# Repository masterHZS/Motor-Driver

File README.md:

# 电机驱动项目 — 总索引

**HC32F005 单板三相无刷电机驱动**

当前主线：

```text
上位机 HostSoftware
  -> USB-TTL / DAPLink 虚拟串口
  -> F005_Slave（Modbus-RTU 从站，地址 1）
  -> 20 kHz PWM 三相功率级
  -> 2216-730KV 三相无刷电机
```

工作方法见 `工作流程.txt`。每个顶层目录均有本地 `00_索引.md`。

> 🤖 **AI / 自动化代理首次进入请先读 `00_AI/START_HERE.md`**（入口与硬禁令）；
> 机器可读清单在 `00_AI/manifest.json`，根目录 `AGENTS.md` 是自动加载的入口钩子。

---

## 1. 顶层顺序与标签

| 顺序 | 目录 | 标签 | 内容 |
|---:|---|---|---|
| 00 | `00_AI/` | AI 入口、现状快照 | ★ **AI 首读**：入口说明、项目地图、当前状态、权威文件速查、构建命令、踩坑与硬约束 |
| 01 | `01_PCB/` | 主设计、已冻结、审核 | V3.1 原理图、网表、BOM、生成器、审核报告 |
| 02 | `02_固件/` | 主固件、通信、台架 | F005 从机、F072 桥/旧控制器参考 |
| 03 | `03_上位机/` | 主软件、Modbus 主站 | Qt 6 + QML 源码与 Release |
| 04 | `04_工作区/` | 调试、波形、审核、工具 | 波形、日志、Gerber 审核、ISP 工具 |
| 05 | `05_采购清单/` | 采购、执行记录 | 采购申请单 |
| 06 | `06_参考资料/` | 唯一资料库 | 芯片知识库、开源参考、EasyEDA、历史会话 |
| 99 | `99_归档/` | 历史、待评估删除 | 旧固件和旧版图备份 |

标签含义：

- `[主]`：当前维护和交付入口。
- `[冻结]`：已作为当前硬件依据，不随意修改。
- `[参考]`：用于查阅或对照，不进入主构建。
- `[调试]`：实测数据和过程记录。
- `[历史]`：只作追溯，可能清理。
- `[可重建]`：构建产物、缓存或派生产物。

---

## 2. 推荐查看顺序

0. `00_AI/START_HERE.md` → `00_AI/02_当前状态.md`（AI 与首次接触者入口）
1. `01_PCB/00_索引.md`
2. `01_PCB/说明.md`
3. `01_PCB/Motor-project/V3.1_升级说明.md`
4. `01_PCB/Motor-project/V3.0_设计规格与计算书.md`
5. `01_PCB/Motor-project/motor-driver-V3.1.*`
6. `01_PCB/Motor-analysis/HC32F005_引脚分配.md`
7. `02_固件/00_索引.md`
8. `02_固件/F005_COMMS.md`
9. `02_固件/F072_MotorCtrl/README.md`
10. `03_上位机/00_索引.md` 与 `03_上位机/HostSoftware/README.md`
11. `04_工作区/00_索引.md`
12. `06_参考资料/00_索引.md`

> ⚠️ **路径提示**：旧文档里写的 `01_PCB/01_工程/` = 现在的 **`01_PCB/Motor-project/`**，
> `01_PCB/03_审核/` = 现在的 **`01_PCB/Motor-analysis/`**（2026-10 改名，历史记录未逐一改写）。

---

## 3. 当前主链路

### 硬件

- 当前版本：**V3.1**（原理图冻结、PCB 已打样；板上 F005 已拆除，改外接 F072 直驱）
- 母线：12.0–16.8 V，4S（有效窗口 13.5–16.8 V）
- 主控：HC32F005C6PA（板上位号 U5，**当前空位**）
- 栅驱动：FD6288T
- 当前控制器：外接 **HC32F072JATA** → `TP12`–`TP17`（见 `02_固件/F072_MotorCtrl/`）

### F005 从机

- 默认构建：`02_固件/F005_Slave/build_comms.ps1`
- 默认输出：`02_固件/F005_Slave/build_comms/comms.hex`
- 通信：UART0，`9600-8N1`，Modbus-RTU 地址 1
- 控制：`0x0002` 油门 0～100
- 实际占空比：默认限幅到 25%
- 开环电换相范围：默认 10～120 Hz
- 非零油门隐式启动，零油门停止
- 烧录恢复：`flash_under_reset.ps1`

### 上位机

- 源码：`03_上位机/HostSoftware/`
- 发布版：`03_上位机/release/HostSoftware/`
- 功能码：`0x03` 读寄存器、`0x06` 写单寄存器
- 状态轮询：`0x0000～0x0009`

---

## 4. 目录维护规则

1. 顶层目录保持两位数字前缀，按开发顺序排列。
2. 每个顶层目录使用 `00_索引.md` 说明标签、内容、顺序和清理规则。
3. 源码工程不按外观随意改名；优先通过索引分类，防止硬编码路径失效。
4. 数据手册和芯片结论只写入 `06_参考资料/芯片知识库/`。
5. 第三方完整工程只写入 `06_参考资料/开源参考工程/`。
6. 构建产物、`__pycache__`、`.pyc`、临时日志可重建或可删除。
7. 历史版本进入 `99_归档/`，不要与当前版本混放。
8. 同内容文件不再保存多份实体副本。
9. `00_AI/` 是 AI 入口与现状快照，只写「指针 + 状态」，不复制权威数据；状态变化后同步更新。

---

## 5. 2026-09-30 整理结果

- F005 主目录收敛为：`build_comms + cmsis + core + ldscripts + port + third_party + user`。
- 删除另一套精简 DDL，只保留官方完整 DDL。
- 删除历史 `build_*`、探针源码、旧 release、便携 Python、测试临时文件。
- 删除根 `$null`、`02_固件/%SystemDrive%`、旧锁文件和可重建缓存。
- `asac-esc` 从固件主目录移到 `06_参考资料/开源参考工程/`。
- 重复 HC32F005 手册合并到 `06_参考资料/芯片知识库/_datasheet/`。
- 所有顶层目录增加 `00_索引.md`，统一标签和推荐查看顺序。

---

## 6. 当前状态

| 项目 | 状态 |
|---|---|
| PCB V3.1 | 已冻结并打样，实板调试中（详见 `01_PCB/说明.md`） |
| 板上 F005 | **已拆除**（UART 固件释放 P27 后 SWD 无法恢复，板上无 nRESET 可用） |
| 当前主链路 | HostSoftware → DAPLink 串口 → **外接 F072_MotorCtrl (`-Direct`)** → V3.1 功率级 |
| F005 直连 Modbus 从站 | 已实现并成功构建（005 拆板前验证通过，保留参考） |
| 上位机油门写 `0x0002` | 已接通 F072 直接油门控制 |
| 电机带载验证 | 尚未完成，必须限流并从低油门开始 |
| 开环版带电机 | ⛔ **已明令禁止**（2026-10-08 剧烈震动事故），必须用 BEMF 闭环 |
| BEMF 闭环 | `F072_MotorCtrl -BEMF`，ADC 通道映射已验证，待整机联调 |

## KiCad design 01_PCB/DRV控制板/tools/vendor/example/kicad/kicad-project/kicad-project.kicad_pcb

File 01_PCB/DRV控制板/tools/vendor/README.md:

中文 | [English](README.en.md)

# kicad-to-easyeda-eprj3

将 KiCAD 工程文件转换为嘉立创EDA（EasyEDA Pro）的 eprj3 工程格式，并将 KiCad 库转换为嘉立创EDA库文件 `.elibz2`。Convert KiCAD project files to the eprj3 project format of EasyEDA Pro, and KiCad libraries to the EasyEDA Pro library format `.elibz2`.

## 功能

- **工程转换**：批量遍历目录下所有 `.kicad_sch` / `.kicad_pcb`，生成完整的 eprj3 文件夹工程（`<name>.eprj3` 索引 + `sch/` + `pcb/`）
- **库转换**：把一个目录下的全部 KiCad 库（`*.kicad_sym` 符号库 + `*.pretty/*.kicad_mod` 封装库）打包成一个嘉立创EDA专业版库文件 `.elibz2`

## 环境要求

- Node.js ≥ 18，无任何 npm 依赖。

## 用法

### 1) KiCad 工程 → eprj3 工程（批量）

```bash
node scripts/convert-kicad.js convert <KiCad工程目录> <输出目录> [--project-name <名称>]
```

案例 — 转换本仓库自带的示例工程：

```bash
node scripts/convert-kicad.js convert example/kicad/kicad-project ./eprj3 --project-name kicad-project
```

输出：

```text
Created eprj3 project at D:/…/eprj3
  sch: kicad-project.kicad_sch -> D:/…/eprj3/sch/Schematic1/P1.esch2
  pcb: kicad-project.kicad_pcb -> D:/…/eprj3/pcb/PCB1.epcb2
```

生成的工程可直接用嘉立创EDA专业版打开：`<输出目录>/kicad-project.eprj3`，内含 `sch/`（原理图）与 `pcb/`（PCB）。

- 两个目录按位置传入：第 1 个是 KiCad 工程目录，第 2 个是 eprj3 输出目录
- 工程目录下每个 `*.kicad_sch` 生成一张原理图（`Schematic1`、`Schematic2` …），每个 `*.kicad_pcb` 生成一块板（`PCB1`、`PCB2` …）

### 2) KiCad 库目录 → 嘉立创EDA库包 .elibz2

```bash
node scripts/convert-kicad-lib.js convert <KiCad库目录> <输出.elibz2> [--name <库名>]
```

案例 — 把符号库与封装库放进同一个目录后整体打包（目录扫描不递归，`.kicad_sym` 与 `.pretty/` 需是直接子项）：

```text
mylibs/
├── Device.kicad_sym
├── LED.kicad_sym
├── Resistor_SMD.pretty/
│   ├── R_0805_2012Metric.kicad_mod
│   └── …
└── LED_SMD.pretty/
    └── …
```

```bash
node scripts/convert-kicad-lib.js convert mylibs ./DeviceLED.elibz2 --name DeviceLED
```

输出：

```text
  sym lib: Device.kicad_sym (533 symbols)
  sym lib: LED.kicad_sym (63 symbols)
  footprint lib: LED_SMD.pretty (100 footprints)
  footprint lib: Resistor_SMD.pretty (67 footprints)
Wrote DeviceLED.elibz2: 596 symbols, 167 footprints (636245 bytes)
```

生成的 `DeviceLED.elibz2` 可通过嘉立创EDA专业版的库导入功能安装到本地库中。

- 扫描目录下所有 `*.kicad_sym`（符号库）与 `*.pretty/`（封装库，读取其中 `*.kicad_mod`），全部合并写入**一个** `.elibz2`
- `--name` 可选：覆盖包名（默认取输出文件名去掉 `.elibz2` 后缀）
- `.elibz2` 是 zip 压缩包，内含：
  - `device2.json` — 器件/符号/封装索引（uuid → 元数据）；符号 `docType:2`、封装 `docType:4`，每个符号自动生成一个器件条目
  - `<库名>.elibu` — 记录流（与 `.esch2`/`.epcb2` 同格式），每个符号/封装写成两段：`DOCHEAD+META` 与 `DOCHEAD+记录`
- 符号 `Footprint` 属性（如 `Resistor_SMD:R_0805`）与转换出的封装名匹配时，器件的 `Footprint` 属性自动关联到对应封装 uuid
- 电源符号（`symbol_type "power"`）的 META `docType` 写为 18；封装文档包含 19 层表 + `ACTIVE_LAYER` + 完整 `CANVAS`，且不带 `PART` 记录
- 示例：`example/easyeda/easyeda-pro-libs.elibz2` 为嘉立创EDA专业版导出的参考库包

## 转换覆盖范围（best-effort）

输出严格对齐 [easyeda-pro-format-skill](https://github.com/easyeda/easyeda-pro-format-skill) 的官方格式文档（types / 字段定义 / JSON Schemas），并以真实导出数据校准 schema 与实际导出不一致之处；可另参考 [官方 eprj3 格式示例工程](https://github.com/easyeda/easyeda-pro-eprj3-format)：

| KiCad | eprj3 |
| --- | --- |
| `lib_symbols`（原理图内嵌符号库） | `.esch2` 内嵌 `SYMBOL` 文档段（`PART`/图形/引脚）+ `DEVICE` 文档段 |
| `symbol` 实例（含 `property`、`mirror`） | `COMPONENT`（`partId` 指向内嵌 `PART`，`DeviceName` 指向 `DEVICE`，镜像/旋转已换算）+ `Designator`/`Value` `ATTR` |
| `wire` | `WIRE` + 多条共享 `lineGroup` 的 `LINE` |
| `bus` / `bus_entry` | `BUS` + `LINE` / `BUSENTRY` |
| `junction` | 填充 `CIRCLE`（电气节点） |
| `no_connect` | 两条 `LINE`（X 标记） |
| `label` / `global_label` / `hierarchical_label` | `NETLABEL` |
| `text` / `text_box` | `TEXT`（+ `RECT` 边框） |
| `polyline` / `rectangle` / `circle` / `arc` / `bezier` | `POLY` / `RECT` / `CIRCLE` / `ARC`（三点求圆心）/ `BEZIER`，stroke/fill 样式同步映射 |
| `image` | `OBJ`（base64 内嵌） |
| `sheet`（层次图） | `RECT` + 名称 `TEXT` + 引脚 `NETLABEL` |
| 引脚电气/图形类型 | `PIN.electric` / `PIN.pinShape` 数值映射 |
| `footprint`（含 `pad`） | `.epcb2` 内嵌 `FOOTPRINT` 文档段（`PART`/`PAD`/丝印图形）+ `DEVICE` 文档段 + `COMPONENT` 放置 + `Designator`/`Footprint`/`Device` `ATTR` |
| pad 网络 / 椭圆孔 | `PAD_NET`（绑定元件引脚）+ `NET` 索引记录 / `holeType ROUND` 宽高 |
| `segment` / `arc`（PCB 走线） | 对应层上的 `FILL`（直线为闭合细多边形；圆弧为带 `ARC` 段的闭合多边形） |
| `via` | `VIA`（网络/孔径/盘径） |
| `zone` | `POUR`（`pourType`/`keepIsland`）+ 每个 `filled_polygon` 合并出的 `POURED`（`pourFill`，head id 关联 `POUR`）；keepout → `REGION`（`regionType PROHIBIT` + `prohibitType`） |
| `dimension`（aligned/orthogonal/radial/leader） | `DIMENSION`（`dimensionType LENGTH-CONSTRAINT` + `controlDot`） |
| `gr_line` / `gr_arc` / `gr_rect` / `gr_poly` / `gr_circle` / `bezier` | `LINE` / `ARC` / 闭合 `POLY`（圆为 `["CIRCLE",…]` 路径、贝塞尔为 `"C"` 段路径） |
| `gr_text` | `STRING`（对齐 origin、镜像、knockout→reverse） |
| `gr_rect`/`gr_line`/`gr_arc`/`gr_poly` on `Edge.Cuts` | 拼接为 `POLY` `BOARD_OUTLINE`（`layerId=11`） |
| 层映射 | `F.Cu=1`、`B.Cu=2`、`F.SilkS=3`、`B.SilkS=4`、`F.Mask=5`、`Edge.Cuts=11`、`In{n}.Cu=14+n`…；PCB 文档写入官方 60 层表 |

- 单位换算：KiCad mm → eprj3 mil（×39.3700787）；坐标轴翻转：KiCad Y 向下 → eprj3 Y 向上；旋转角 (360−deg)%360
- uuid 关联（官方约定）：`.esch2` 页面 / `.epcb2` / `.ecfg` 的 `DOCHEAD.uuid` 分别等于索引中 `sheets` / `pcbs` / `schematics` 的 uuid
- 同时生成 `sch/<名称>/<名称>.ecfg`（设计规则骨架）与 `.evar`（装配变量，空）
- **不迁移**：3D 模型、网络类、SPICE 模型、自定义规则；无法翻译的元素会跳过并告警

### 库转换覆盖范围（.elibz2）

| KiCad 库 | .elibz2 |
| --- | --- |
| `*.kicad_sym` 内每个 `(symbol …)` | `SYMBOL` 文档段（`PART`/`PIN`/`POLY`/`RECT`/`CIRCLE`/`ARC`/`BEZIER`）+ `device2.json` 符号索引 + 器件条目 |
| `symbol_type "power"` | META `docType:18`（电源类） |
| 符号 `property`（Reference/Value 之外的） | 器件 `attributes` 透传 |
| 符号 `Footprint` 属性 | 与封装名匹配时自动写入器件 `attributes.Footprint`（uuid） |
| `*.pretty/*.kicad_mod` 每个 `(footprint …)` | `FOOTPRINT` 文档段（19 层表 + `PAD`/`POLY`/`ARC` + `ACTIVE_LAYER`）+ `device2.json` 封装索引 |
| pad `thru_hole`/`oval` 钻孔 | `PAD` 的 `holeDiameter`/`holeWidth`/`holeType ROUND` |
| `F.SilkS`/`B.SilkS` 图形 | layerId 3/4；Fab/CrtYd/Dwgs 等其余 → Document 层 13 |

## 目录结构

```
kicad-to-easyeda-eprj3/
├── scripts/
│   ├── convert-kicad.js      ← 工程批量转换入口（→ eprj3 工程目录）
│   ├── convert-kicad-lib.js  ← 库转换入口（→ .elibz2 库包）
│   └── lib/
│       ├── kicad.js          ← KiCad S-expression 解析器
│       ├── kicad-to-eprj3.js ← 符号/封装 → eprj3 记录
│       ├── eprj3.js          ← eprj3 读写核心（源自 easyeda-eprj3-skill，已按官方示例修正）
│       ├── elibz2.js         ← .elibz2 库包组装（device2.json + .elibu）
│       ├── zip.js            ← 零依赖 zip 读写（zlib deflate/store）
│       └── utils.js
├── example/
│   ├── easyeda/              ← 嘉立创EDA专业版参考库包 easyeda-pro-libs.elibz2
│   └── kicad/                ← 示例 KiCad 工程
└── test/
    ├── smoke.js              ← 端到端冒烟测试（68 项断言）
    └── validate-format.js    ← 用官方 JSON Schemas 校验生成记录的格式验证器
```

## 测试

```bash
npm test
```

另可用官方 Schemas 逐条校验生成的记录（sch/pcb/lib 三种上下文，lib 按文档 docType 自动路由）：

```bash
node test/validate-format.js <生成的 .esch2|.epcb2|.elibu> <sch|pcb|lib>
```

> 验证器依赖 [easyeda-pro-format-skill](https://github.com/easyeda/easyeda-pro-format-skill) 的 `validate.js`，默认在其同级目录查找；也可通过环境变量 `EASYEDA_FORMAT_SKILL` 指定路径。注：官方 Schemas 与真实导出数据存在少量出入（如 `POUR.pourType`、PCB `ATTR.groupID`、`DIMENSION` 结构等），验证器已按真实导出数据校准。

## 相关项目

- [easyeda-pro-format-skill](https://github.com/easyeda/easyeda-pro-format-skill) — 嘉立创EDA Pro 文件格式技能包（types 索引、图元字段定义、JSON Schemas、validate.js），本仓库的格式权威参考
- [easyeda-eprj3-skill](https://github.com/easyeda/easyeda-eprj3-skill) — 教 AI 编码助手从零生成 `.eprj3` 工程的技能包；本仓库的 `scripts/lib/eprj3.js` 与 `utils.js` 即来自该项目的核心库
- [easyeda-pro-eprj3-format](https://github.com/easyeda/easyeda-pro-eprj3-format) — 官方 eprj3 格式示例工程

## License

[Apache-2.0](LICENSE)

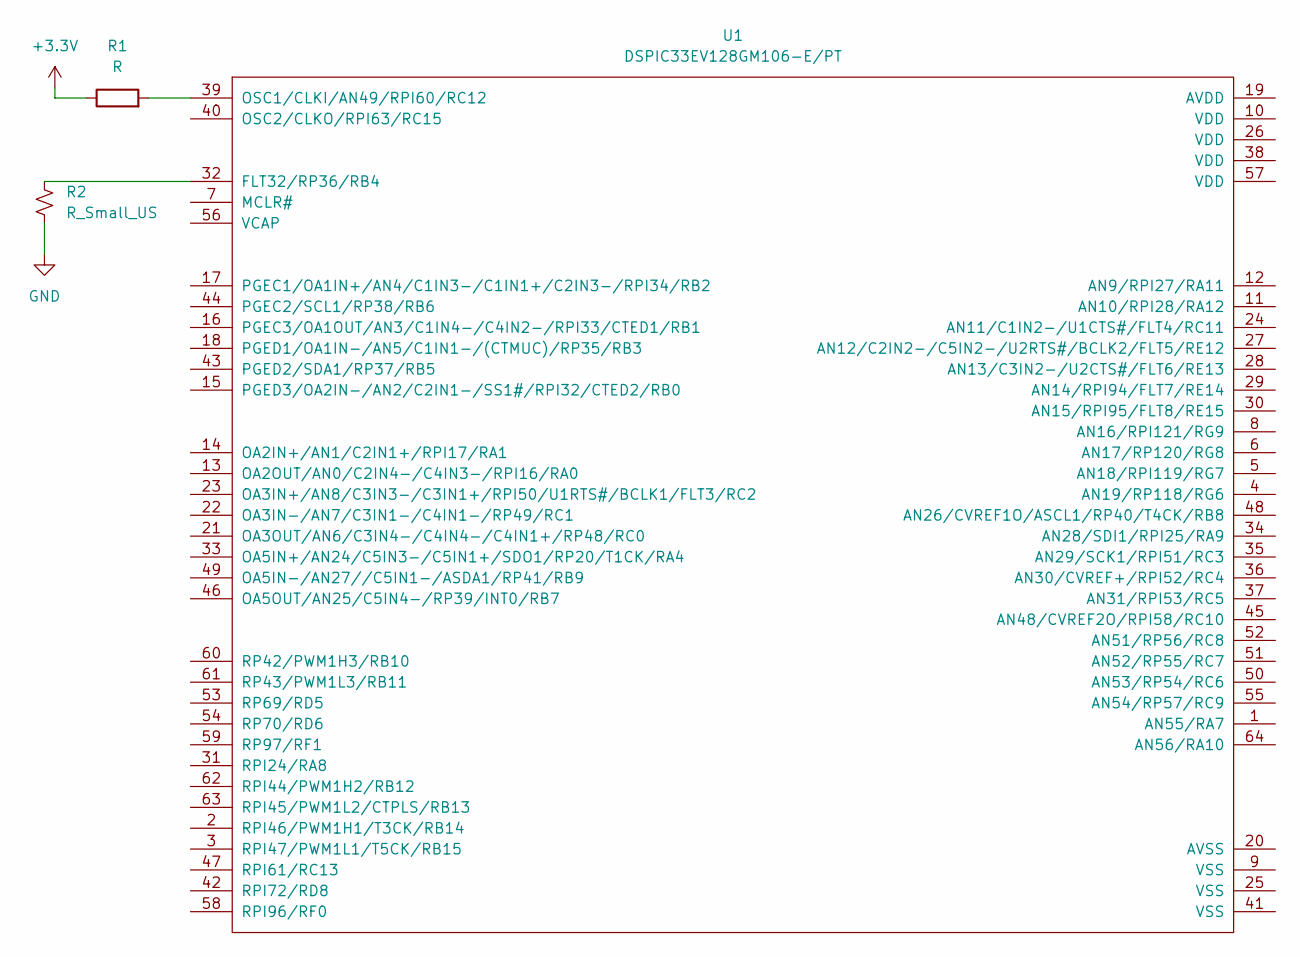
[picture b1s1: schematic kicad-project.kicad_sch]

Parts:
R1: R; R_0603_1608Metric
R2: R_Small_US; R_0805_2012Metric
U1: DSPIC33EV128GM106-E/PT; QFN-56-1EP_8x8mm_P0.5mm_EP4.5x5.2mm_ThermalVias_TopTented

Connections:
+3.3V: R1.1
GND: R2.2
unnamed: R2.1, U1.32 (FLT32/RP36/RB4)
unnamed: R1.2, U1.39 (OSC1/CLKI/AN49/RPI60/RC12)

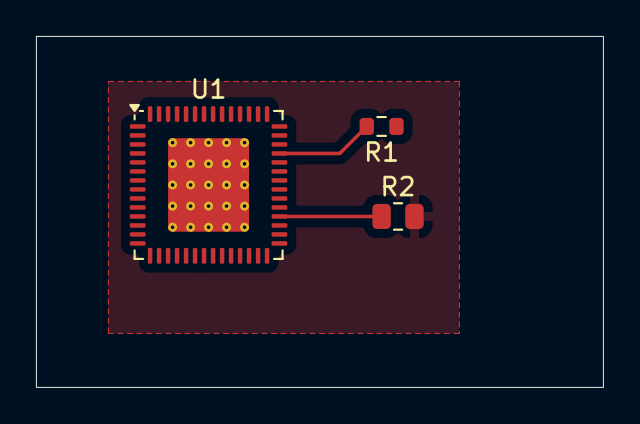
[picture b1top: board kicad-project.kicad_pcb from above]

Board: 2 copper layers, 31.5 x 19.5 mm, 3 parts (0 on the bottom side), 2 nets.
